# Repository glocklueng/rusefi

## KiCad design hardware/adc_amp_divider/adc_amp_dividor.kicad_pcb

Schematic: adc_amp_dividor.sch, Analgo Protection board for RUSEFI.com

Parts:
C210, C220, C230, C240, C250, C260, C270, C280, C290, C300, C310, C320: 0.01uF
C211, C251, C291: 0.1uF
D210, D220, D230, D240, D250, D260, D270, D280, D290, D300, D310, D320: DOUBLE_SCHOTTKY
G200, G201, G202: LOGO
LD200: LED
M200, M201, M202: CONN_1
P201: CONN_10X2
P202, P206: CONN_3
P203, P207: CONN_2; SIL-2
P204, P205: CONN_1
P208, P209: CONN_6
R200, R213, R223, R233, R243, R253, R263, R273, R283, R293, R303, R313, R323: 100
R210, R220, R230, R240, R250, R260, R270, R280, R290, R300, R310, R320: 2700
R211, R221, R231, R241, R251, R261, R271, R281, R291, R301, R311, R321: 500K
R212, R222, R232, R242, R252, R262, R272, R282, R292, R302, R312, R322: 10k
R214, R215, R224, R225, R234, R235, R244, R245, R254, R255, R264, R265, R274, R275, R284, R285, R294, R295, R304, R305, R314, R315, R324, R325: 1500
U201, U202, U203: LMV324IDR
W211, W212: TEST; SIL-2

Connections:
/INP1: P208.6, R210.1, R211.1, R212.1
/INP2: P208.5, R220.1, R221.1, R222.1
/INP3: P208.4, R230.1, R231.1, R232.1
/INP4: P208.3, R240.1, R241.1, R242.1
/INP5: P208.2, R250.1, R251.1, R252.1
/INP6: P208.1, R260.1, R261.1, R262.1
/INP7: P209.6, R270.1, R271.1, R272.1
/INP8: P209.5, R280.1, R281.1, R282.1
/INP9: P209.4, R290.1, R291.1, R292.1
/INP10: P209.3, R300.1, R301.1, R302.1
/INP11: P209.2, R310.1, R311.1, R312.1
/INP12: P209.1, R320.1, R321.1, R322.1
/OUT1: P201.19, R214.2, R215.1
/OUT2: P201.20, R224.2, R225.1
/OUT3: P201.17, R234.2, R235.1
/OUT4: P201.18, R244.2, R245.1
/OUT5: P201.16, R254.2, R255.1
/OUT6: P201.13, R264.2, R265.1
/OUT7: P201.14, R274.2, R275.1
/OUT8: P201.11, R284.2, R285.1
/OUT9: P201.12, R294.2, R295.1
/OUT10: P201.9 (P207), R304.2, R305.1
/OUT11: P201.10, W211.1
/OUT12: P201.7 (P205), W212.1
/PA5: P201.15, P204.1
/PC0: P201.8 (P206), P205.1
GND: C210.1, C211.2, C220.1, C230.1, C240.1, C250.1, C251.2, C260.1, C270.1, C280.1, C290.1, C291.1, C300.1, C310.1, C320.1, D210.1 (Anode), D220.1 (Anode), D230.1 (Anode), D240.1 (Anode), D250.1 (Anode), D260.1 (Anode), D270.1 (Anode), D280.1 (Anode), D290.1 (Anode), D300.1 (Anode), D310.1 (Anode), D320.1 (Anode), LD200.1 (A), P201.1 (P201), P201.2 (P208), P201.5 (P203), P203.1 (P201), P203.2 (PM), P207.1 (P201), P207.2 (PM), R211.2, R215.2, R221.2, R225.2, R231.2, R235.2, R241.2, R245.2, R251.2, R255.2, R261.2, R265.2, R271.2, R275.2, R281.2, R285.2, R291.2, R295.2, R301.2, R305.2, R311.2, R315.2, R321.2, R325.2, U201.11 (GND), U202.11 (GND), U203.11 (GND)
unnamed: D210.2 (AK), R212.2, R213.1
unnamed: D220.2 (AK), R222.2, R223.1
unnamed: C290.2, R293.2, U203.12 (+)
unnamed: C300.2, R303.2, U203.9 (+)
unnamed: D290.2 (AK), R292.2, R293.1
unnamed: D280.2 (AK), R282.2, R283.1
unnamed: D270.2 (AK), R272.2, R273.1
unnamed: D250.2 (AK), R252.2, R253.1
unnamed: D260.2 (AK), R262.2, R263.1
unnamed: D300.2 (AK), R302.2, R303.1
unnamed: R294.1, U203.13 (-), U203.14
unnamed: R304.1, U203.8, U203.10 (-)
unnamed: C320.2, R323.2, U203.5 (+)
unnamed: D320.2 (AK), R322.2, R323.1
unnamed: D310.2 (AK), R312.2, R313.1
unnamed: R314.1, U203.1, U203.2 (-)
unnamed: C310.2, R313.2, U203.3 (+)
unnamed: R324.1, U203.6 (-), U203.7
unnamed: R324.2, R325.1, W212.2
unnamed: R314.2, R315.1, W211.2
unnamed: R284.1, U202.6 (-), U202.7
unnamed: R274.1, U202.1, U202.2 (-)
unnamed: R264.1, U202.8, U202.10 (-)
unnamed: R214.1, U201.13 (-), U201.14
unnamed: R224.1, U201.8, U201.10 (-)
unnamed: R234.1, U201.1, U201.2 (-)
unnamed: R244.1, U201.6 (-), U201.7
unnamed: C250.2, R253.2, U202.12 (+)
unnamed: R254.1, U202.13 (-), U202.14
unnamed: C240.2, R243.2, U201.5 (+)
unnamed: D240.2 (AK), R242.2, R243.1
unnamed: C230.2, R233.2, U201.3 (+)
unnamed: C280.2, R283.2, U202.5 (+)
unnamed: C270.2, R273.2, U202.3 (+)
unnamed: C220.2, R223.2, U201.9 (+)
unnamed: C210.2, R213.2, U201.12 (+)
unnamed: C260.2, R263.2, U202.9 (+)
unnamed: LD200.2 (K), R200.2
unnamed: D230.2 (AK), R232.2, R233.1
VCC: C211.1, C251.1, C291.2, D210.3 (cathode), D220.3 (cathode), D230.3 (cathode), D240.3 (cathode), D250.3 (cathode), D260.3 (cathode), D270.3 (cathode), D280.3 (cathode), D290.3 (cathode), D300.3 (cathode), D310.3 (cathode), D320.3 (cathode), P202.1 (P201), P202.2 (PM), P202.3 (P209), P206.1 (P201), P206.2 (PM), P206.3 (P209), R200.1, R210.2, R220.2, R230.2, R240.2, R250.2, R260.2, R270.2, R280.2, R290.2, R300.2, R310.2, R320.2, U201.4 (V+), U202.4 (V+), U203.4 (V+)

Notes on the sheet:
mountng screws

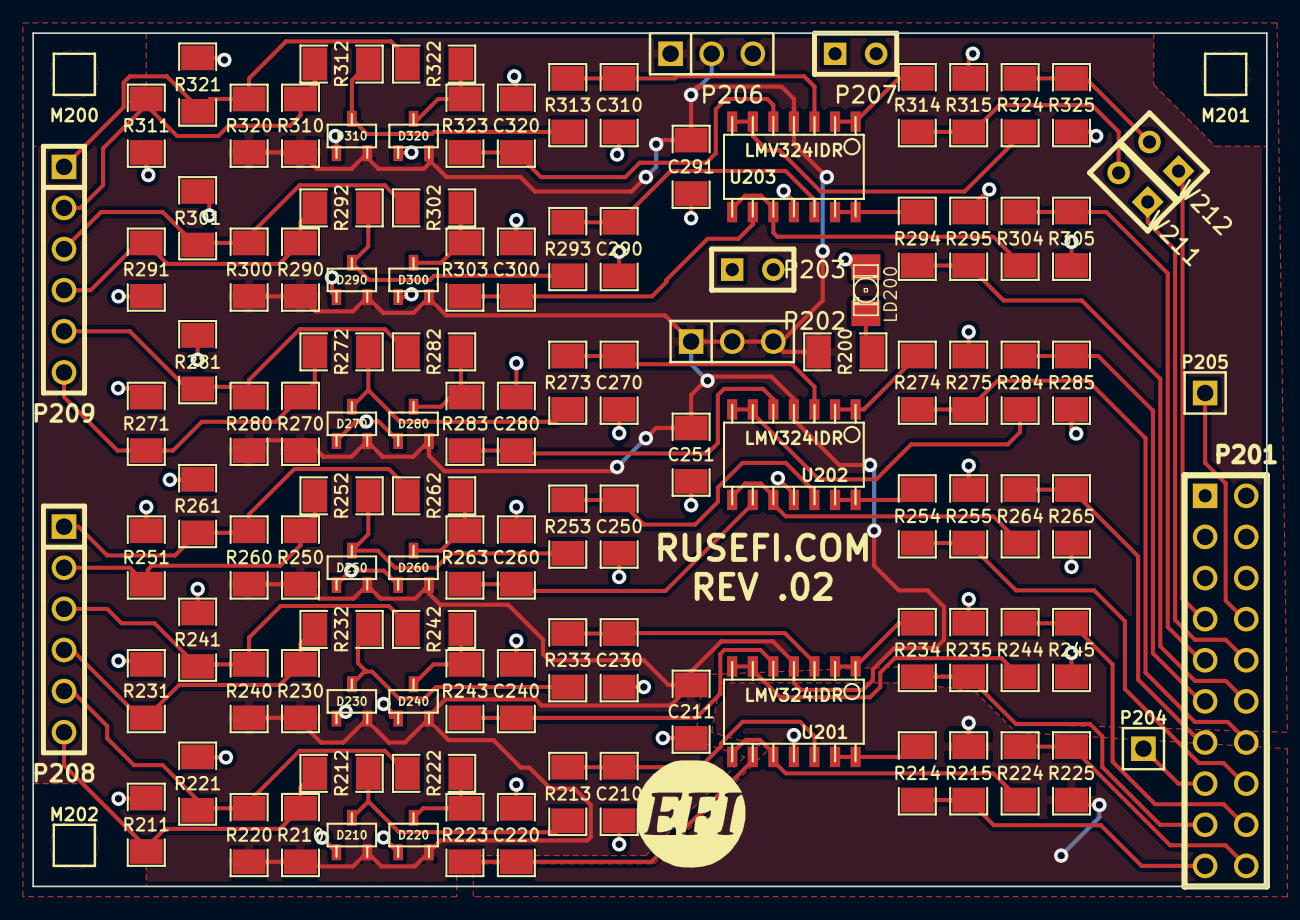
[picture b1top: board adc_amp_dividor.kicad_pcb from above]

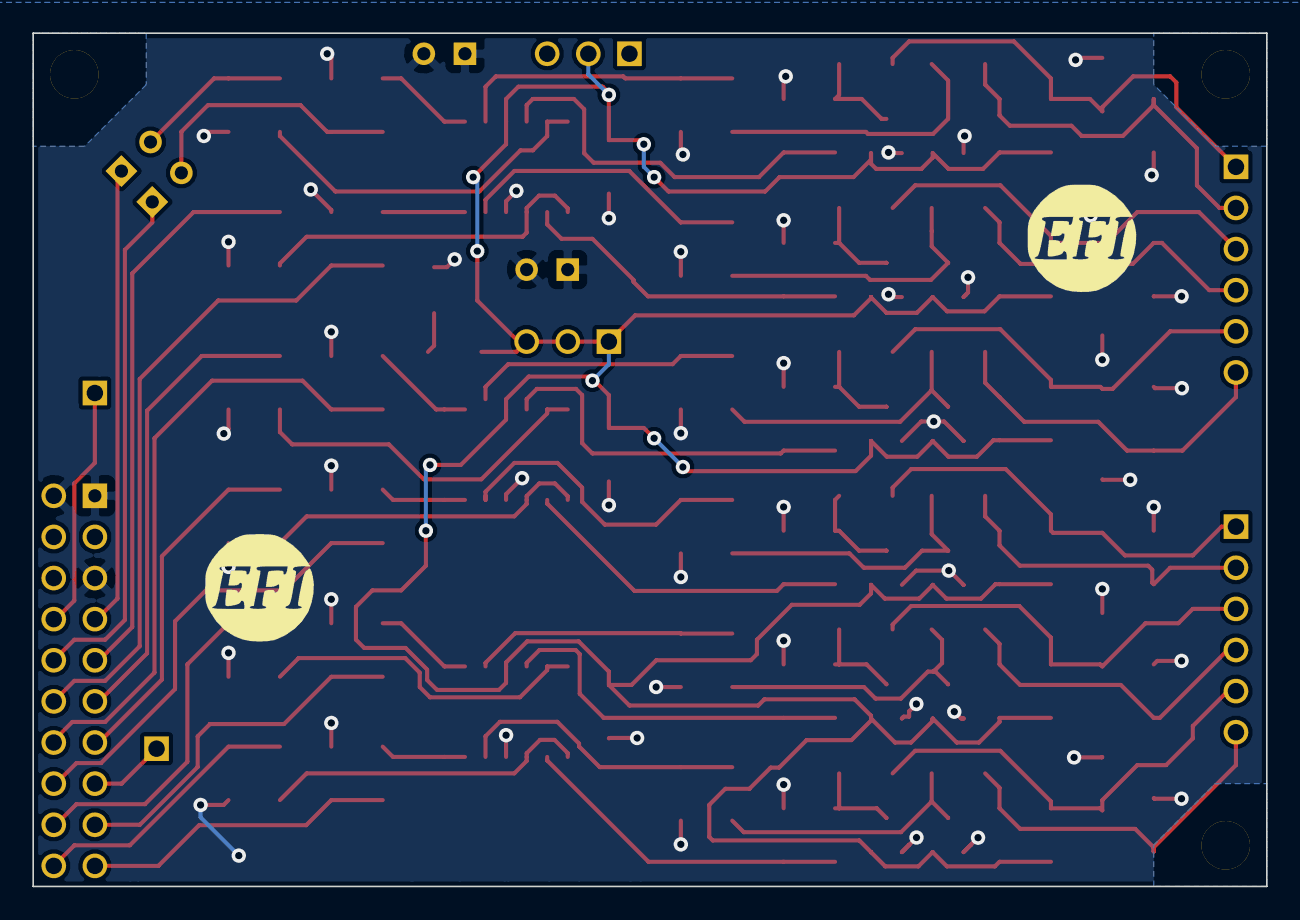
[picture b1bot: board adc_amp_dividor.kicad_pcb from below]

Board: 2 copper layers, 76.2 x 52.7 mm, 121 parts (2 on the bottom side), 67 nets.

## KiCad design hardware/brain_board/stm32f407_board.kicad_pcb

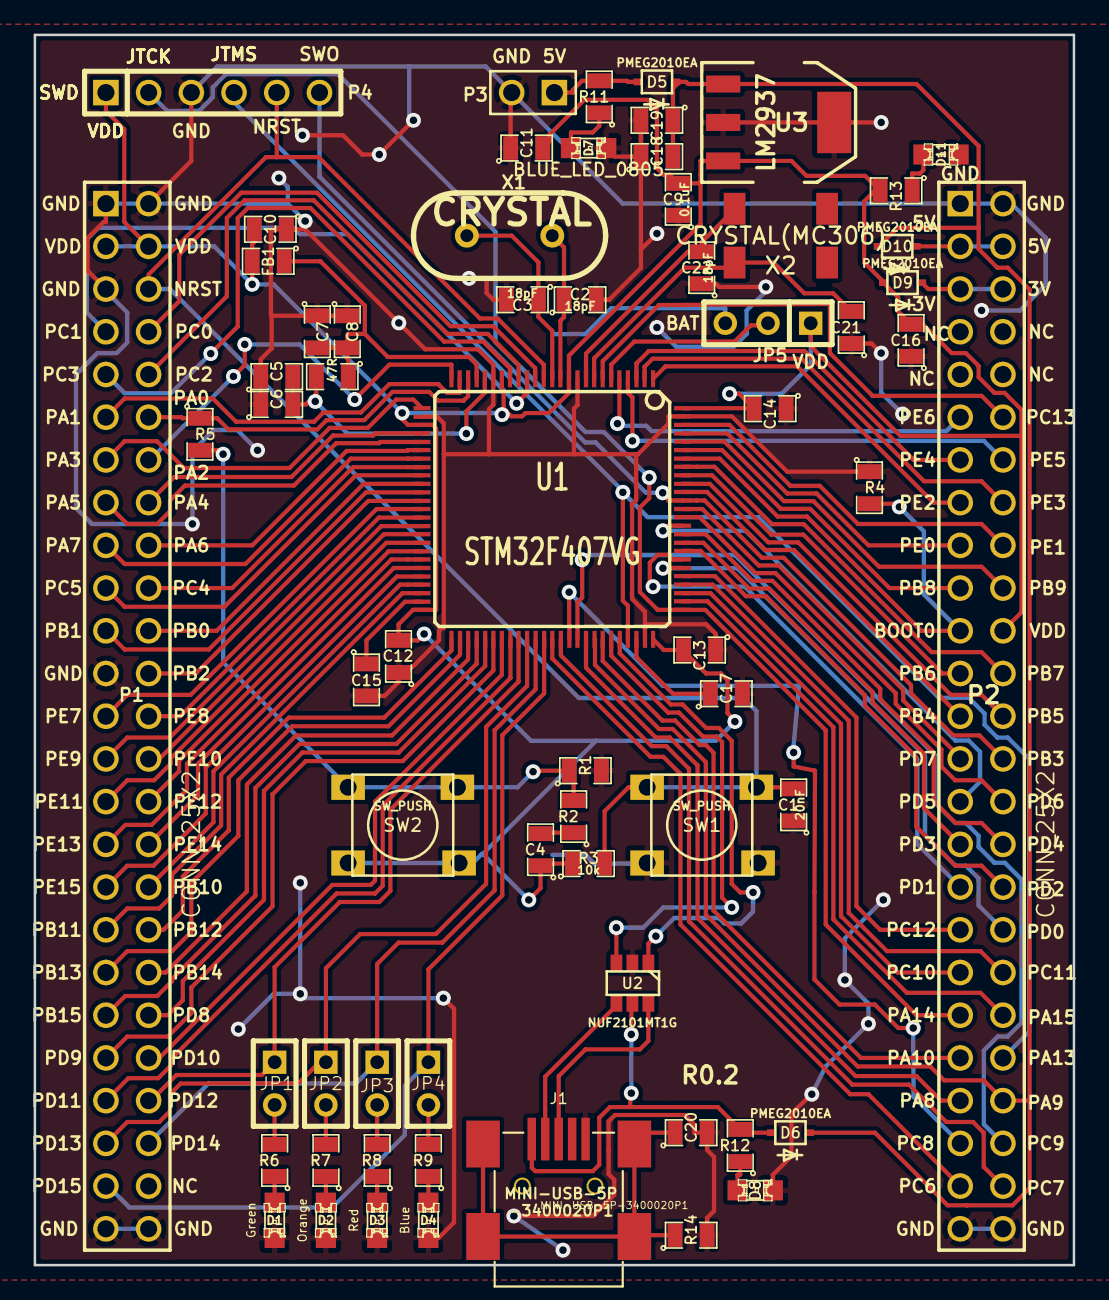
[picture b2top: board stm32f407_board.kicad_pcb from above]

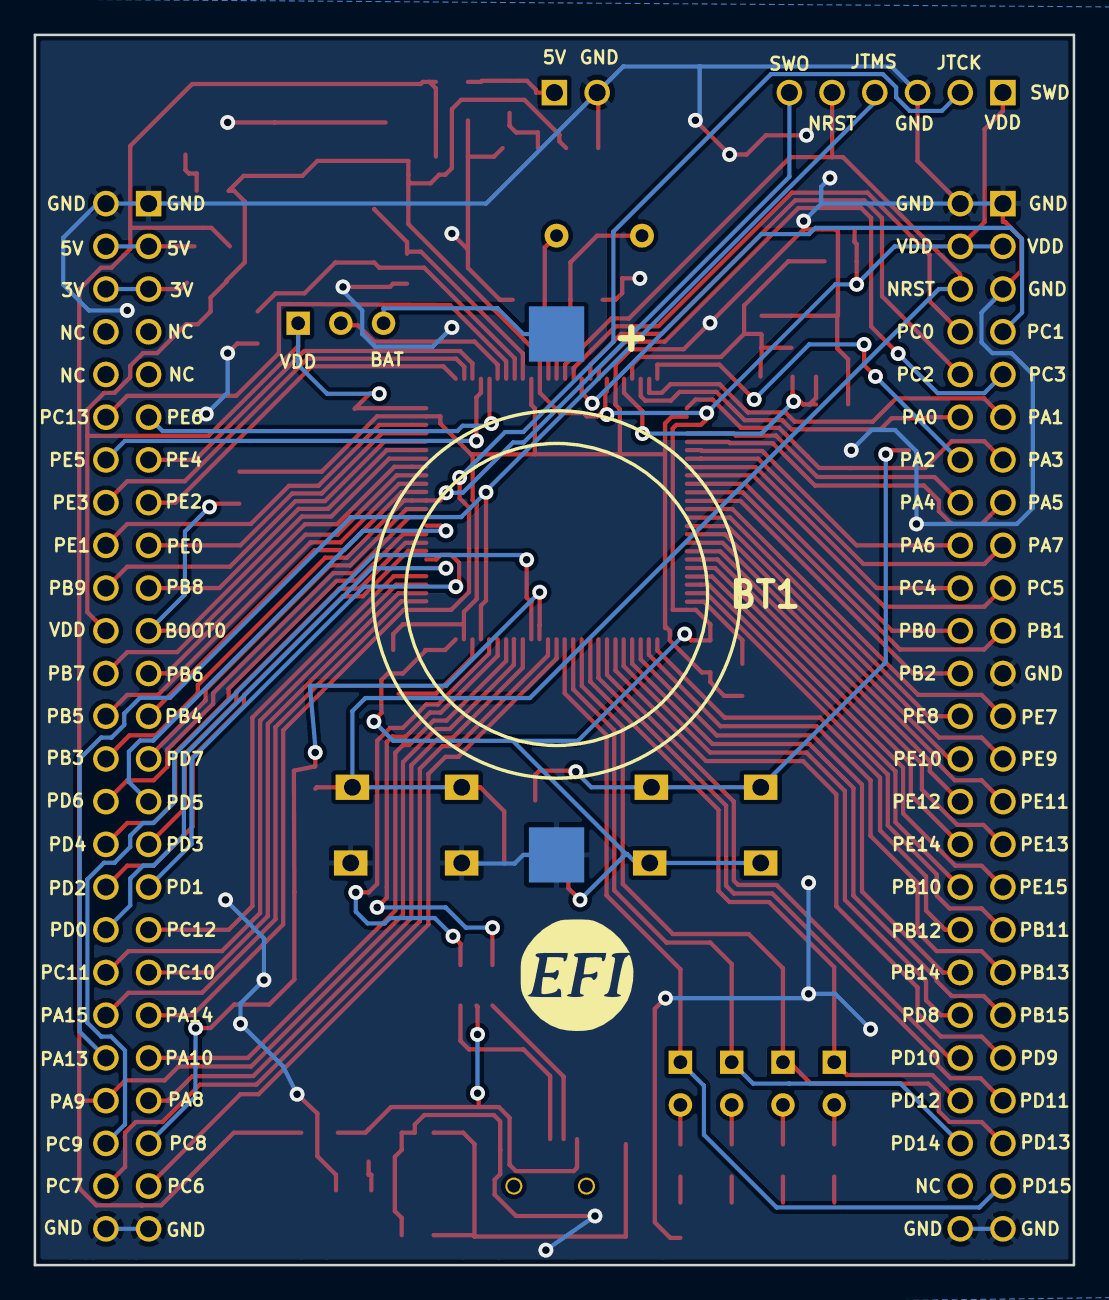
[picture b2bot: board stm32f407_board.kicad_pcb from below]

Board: 2 copper layers, 61.8 x 73.2 mm, 67 parts (2 on the bottom side), 112 nets.

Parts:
BT1: BATTERY_CR2032; BATT_CR2032_MPD
C1: 20nF; SM0805
C2, C3, C21, C22: 18pF; SM0805
C4, C15, C17: 2u2F; SM0805
C5, C8: 0.01uF; SM0805
C6, C7, C16: 1uF; SM0805
C9, C10, C11, C12, C13, C14, C18, C20: 0.1uF; SM0805
C19: 4.7uF; SM0805
D1, D2, D3, D4, D7, D8, D11: BLUE_LED_0805; LED-0805_A
D5, D6, D9, D10: PMEG2010EA; SOD-323
FB1: FILTER; SM0805
G1: LOGO; LOGO_F
J1: MINI-USB-5P-3400020P1
JP1, JP2, JP3, JP4: JUMPER; JUMPER-2
JP5: JUMPER3; SIL-3
P1, P2: CONN_25X2; PIN_ARRAY_25x2_A
P3: CONN_2; PIN_ARRAY_2_A
P4: CONN_6; PIN_ARRAY-6X1
R1, R3, R4: 10k; SM0805
R2: 100R; SM0805
R5: 330R; SM0805
R6, R7, R8, R9: 680R; SM0805
R10: 47R; SM0805
R11, R12, R13: 1k; SM0805
R14: 100k; SM0805
SW1, SW2: SW_PUSH; TL-1105
U1: STM32F407VG; TQFP_100
U2: NUF2101MT1G; SOT-457
U3: LM2937; SOT223
X1: CRYSTAL; HC-49V
X2: CRYSTAL(MC306); MC-306

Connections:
/3V: D9.2, P2.5, P2.6
/5V: D10.2, P2.3, P2.4
/5Vi: C18.2, C19.1, D5.2, D6.2, D10.1, P2.44, U1.68, U3.1
/BOOT0: P2.21, R4.2, U1.94
/D+: J1.3, U2.6
/D-: J1.2, U2.4
/NRST: C1.2, P1.6, P4.5, R3.2, SW1.1, U1.14
/PA0: P1.12, R5.1, U1.23
/PA1: P1.11, U1.24
/PA2: P1.14, U1.25
/PA3: P1.13, U1.26
/PA4: P1.16, U1.29
/PA5: P1.15, U1.30
/PA6: P1.18, U1.31
/PA7: P1.17, U1.32
/PA8: P2.43, U1.67
/PA10: P2.41, U1.69
/PA11: U1.70, U2.3
/PA12: U1.71, U2.1
/PA13: P2.42, P4.4, U1.72
/PA14: P2.39, P4.2, U1.76
/PA15: P2.40, U1.77
/PB0: P1.22, U1.35
/PB1: P1.21, U1.36
/PB2: P1.24, U1.37
/PB3: P2.28, P4.6, U1.89
/PB4: P2.25, U1.90
/PB5: P2.26, U1.91
/PB6: P2.23, U1.92
/PB7: P2.24, U1.93
/PB8: P2.19, U1.95
/PB9: P2.20, U1.96
/PB10: P1.34, U1.47
/PB11: P1.35, U1.48
/PB12: P1.36, U1.51
/PB13: P1.37, U1.52
/PB14: P1.38, U1.53
/PB15: P1.39, U1.54
/PC0: P1.8, U1.15
/PC1: P1.7, U1.16
/PC2: P1.10, U1.17
/PC3: P1.9, U1.18
/PC4: P1.20, U1.33
/PC5: P1.19, U1.34
/PC6: P2.47, U1.63
/PC7: P2.48, U1.64
/PC8: P2.45, U1.65
/PC9: P2.46, U1.66
/PC10: P2.37, U1.78
/PC11: P2.38, U1.79
/PC12: P2.35, U1.80
/PC13: P2.12, U1.7
/PD0: P2.36, U1.81
/PD1: P2.33, U1.82
/PD2: P2.34, U1.83
/PD3: P2.31, U1.84
/PD4: P2.32, U1.85
/PD5: P2.29, U1.86
/PD6: P2.30, U1.87
/PD7: P2.27, U1.88
/PD8: P1.40, U1.55
/PD9: P1.41, U1.56
/PD10: P1.42, U1.57
/PD11: P1.43, U1.58
/PD12: JP1.1, P1.44, U1.59
/PD13: JP2.1, P1.45, U1.60
/PD14: JP3.1, P1.46, U1.61
/PD15: JP4.1, P1.47, U1.62
/PE0: P2.17, U1.97
/PE1: P2.18, U1.98
/PE2: P2.15, U1.1
/PE3: P2.16, U1.2
/PE4: P2.13, U1.3
/PE5: P2.14, U1.4
/PE6: P2.11, U1.5
/PE7: P1.25, U1.38
/PE8: P1.26, U1.39
/PE9: P1.27, U1.40
/PE10: P1.28, U1.41
/PE11: P1.29, U1.42
/PE12: P1.30, U1.43
/PE13: P1.31, U1.44
/PE14: P1.32, U1.45
/PE15: P1.33, U1.46
/VDD: C4.1, C9.2, C10.2, C11.2, C12.2, C13.2, C14.2, C16.2, D9.1, FB1.2, JP5.1, P1.3, P1.4, P2.22, P4.1, R3.1, R13.2, SW2.2, U1.11, U1.19, U1.28, U1.50, U1.75, U1.100, U3.3
/Vbus: D6.1, J1.1, R12.2, U2.5
GND: BT1.2, C1.1, C2.2, C3.2, C5.1, C6.1, C7.1, C8.1, C9.1, C10.1, C11.1, C12.1, C13.1, C14.1, C15.2, C16.1, C17.2, C18.1, C19.2, C20.2, C21.1, C22.1, D1.2, D2.2, D3.2, D4.2, D7.2, D8.2, D11.2, J1.5, P1.1, P1.2, P1.5, P1.23, P1.49, P1.50, P2.1, P2.2, P2.49, P2.50, P3.2, P4.3, R1.2, R4.1, R14.2, SW1.2, U1.10, U1.20, U1.27, U1.74, U1.99, U2.2, U3.2, U3.4
unnamed: JP5.2, U1.6
unnamed: BT1.1, JP5.3
unnamed: JP1.2, R6.2
unnamed: C4.2, R2.1
unnamed: R1.1, R2.2, R5.2, SW2.1
unnamed: JP2.2, R7.2
unnamed: JP3.2, R8.2
unnamed: JP4.2, R9.2
unnamed: D7.1, R11.1
unnamed: D5.1, P3.1, R11.2
unnamed: D8.1, R12.1
unnamed: D1.1, R6.1
unnamed: D2.1, R7.1
unnamed: D3.1, R8.1
unnamed: D4.1, R9.1
unnamed: D11.1, R13.1
unnamed: C20.1, J1.6, R14.1
unnamed: C5.2, C6.2, R10.2, U1.21
unnamed: C21.2, U1.8, X2.1
unnamed: C22.2, U1.9, X2.4
unnamed: C3.1, U1.13, X1.1
unnamed: C17.1, U1.73
unnamed: C2.1, U1.12, X1.2
unnamed: C15.1, U1.49
unnamed: C7.2, C8.2, FB1.1, R10.1, U1.22

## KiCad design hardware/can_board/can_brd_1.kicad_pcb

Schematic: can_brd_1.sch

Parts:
C471: .1uF
C472: 4.7uF
D471: RED
G471: LOGO
JP471: JUMPER
M470, M471: CONN_1
P1, P472: CONN_2
P471: CONN_4
R471: 1k
R472: 10k
R473: 120
U471: SN65HVD230

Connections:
/3.3V: C471.2, C472.1, P471.1, R471.2, U471.3 (VCC)
/CANH: P1.2 (PM), P472.2 (PM), R473.2, U471.7 (CANH)
/CANL: JP471.2, P1.1, P472.1, U471.6 (CANL)
/CAN_RX: P471.3, U471.4 (R/RXD)
/CAN_TX: P471.4, U471.1 (D/TXD)
GND: C471.1, C472.2, D471.2 (K), P471.2, R472.2, U471.2 (GND)
unnamed: D471.1 (A), R471.1
unnamed: JP471.1, R473.1
unnamed: R472.1, U471.8 (RS)

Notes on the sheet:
CAN level shifter
pins

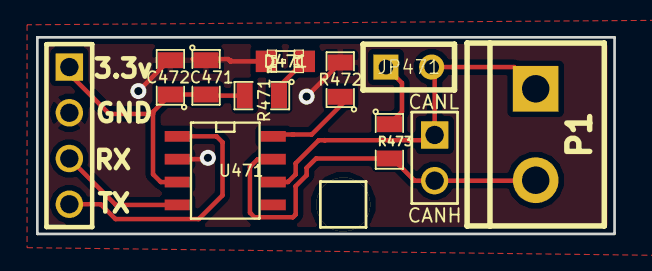
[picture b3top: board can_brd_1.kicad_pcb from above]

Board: 2 copper layers, 32.1 x 10.9 mm, 13 parts (1 on the bottom side), 9 nets.

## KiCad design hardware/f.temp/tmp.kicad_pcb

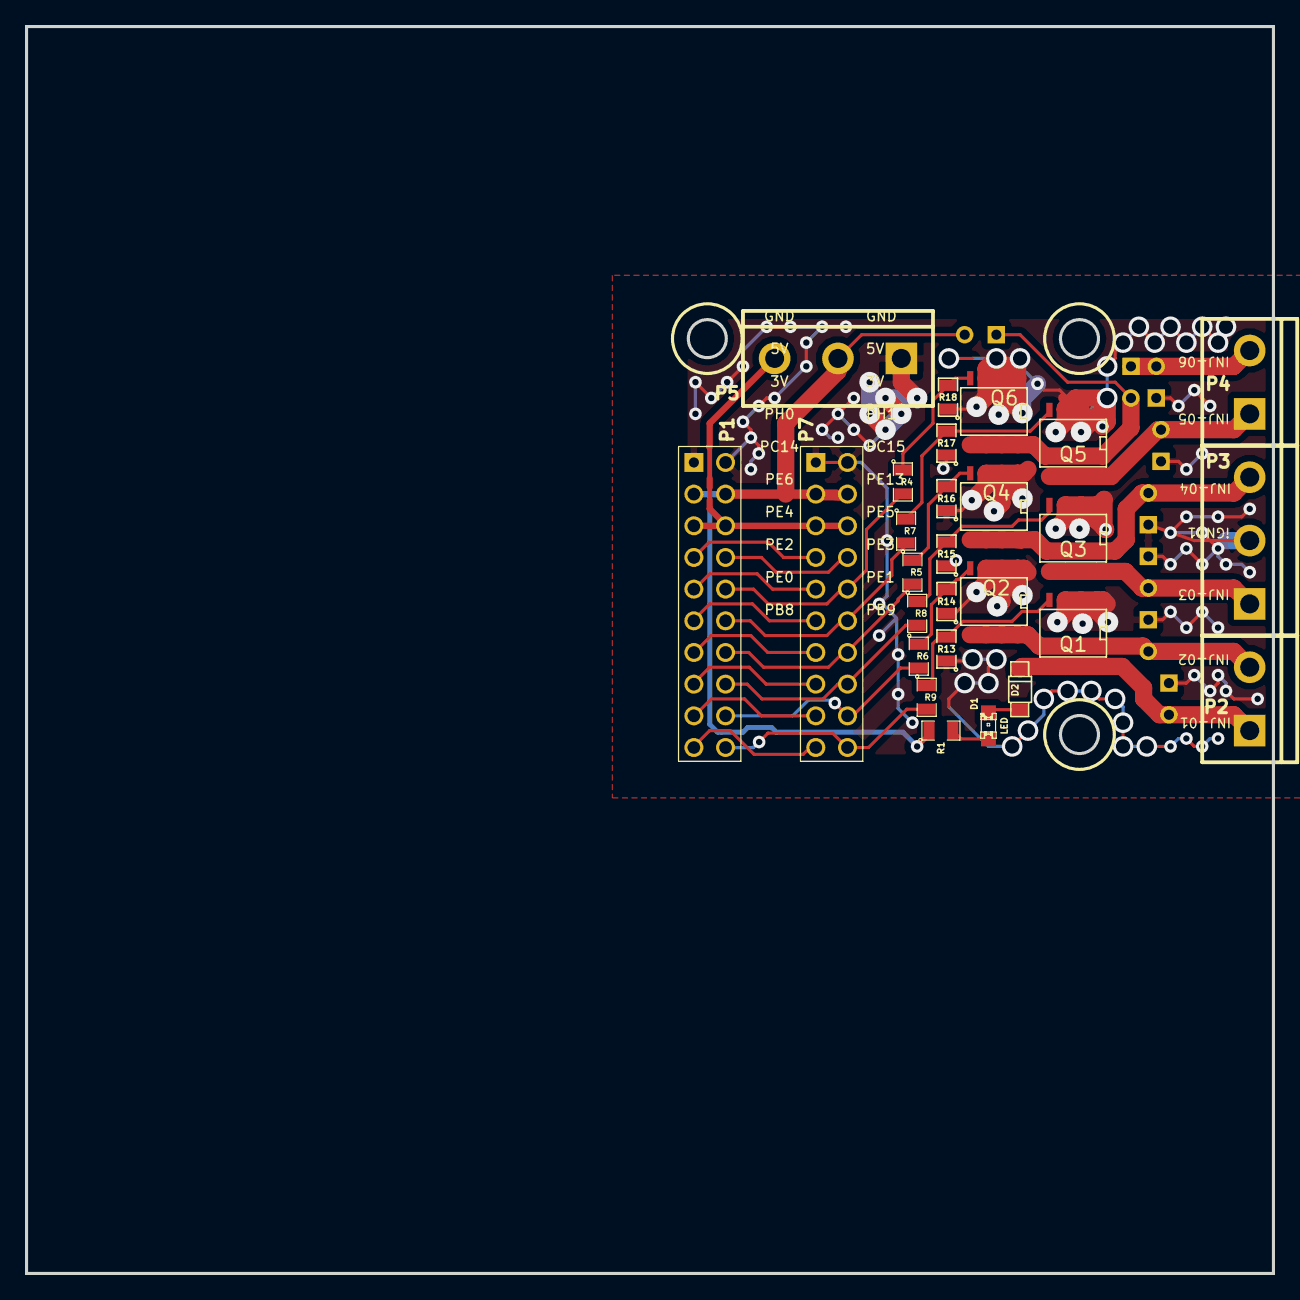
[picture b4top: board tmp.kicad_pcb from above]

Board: 2 copper layers, 100.0 x 100.0 mm, 35 parts (0 on the bottom side), 32 nets.

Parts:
D1: LED; LED-0805
D2: DIODE; SOD-123
D3, D4, D5, D6, D7, D8: DIODE; SIL-2
P1, P7: CONN_10X2; pin_array_10x2
P2, P4: CONN_2; bornier2
P3, P5: CONN_3; bornier3
Q1, Q2, Q3, Q4, Q5, Q6: OVP_DRIVER; SO8E_ST
R1, R13, R14, R15, R16, R17, R18: 1K; SM0805
R2: OPT; SIL-2
R3: 0R; SIL-2
R4, R5, R6, R7, R8, R9: 20R; SM0805

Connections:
/3V: P1.5, P1.6, P5.3, P7.5, P7.6
/5V: P1.3, P1.4, P5.2, P7.3, P7.4, R1.1, R2.2
/INJ-01: D2.2, D8.2, P2.1, Q1.2
/INJ-01_5V: P1.20, P7.20, R9.2
/INJ-02: D5.2, P2.2, Q2.2
/INJ-02_5V: P1.18, P7.18, R6.2
/INJ-03: D7.2, P3.1, Q3.2
/INJ-03_5V: P1.16, P7.16, R8.2
/INJ-04: D4.2, P3.3, Q4.2
/INJ-04_5V: P1.14, P7.14, R5.2
/INJ-05: D6.2, P4.1, Q5.2
/INJ-05_5V: P1.12, P7.12, R7.2
/INJ-06: Q6.2, R2.1, R3.2
/INJ-06_2: D3.2, P4.2, R3.1
/INJ-06_5V: P1.10, P7.10, R4.2
/PB8: P1.19, P7.19
/PC14: P1.9, P7.9
/PE0: P1.17, P7.17
/PE2: P1.15, P7.15
/PE4: P1.13, P7.13
/PE6: P1.11, P7.11
/PH0: P1.7, P7.7
/PH1: P1.8, P7.8
GND: D3.1, D4.1, D5.1, D6.1, D7.1, D8.1, P1.1, P1.2, P3.2, P5.1, P7.1, P7.2, Q1.3, Q2.3, Q3.3, Q4.3, Q5.3, Q6.3, R13.1, R14.1, R15.1, R16.1, R17.1, R18.1
unnamed: D1.1, R1.2
unnamed: D1.2, D2.1
unnamed: Q6.1, R4.1, R18.2
unnamed: Q4.1, R5.1, R16.2
unnamed: Q3.1, R8.1, R15.2
unnamed: Q2.1, R6.1, R14.2
unnamed: Q1.1, R9.1, R13.2
unnamed: Q5.1, R7.1, R17.2
